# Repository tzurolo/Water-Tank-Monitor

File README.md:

# Water Tank Monitor
Monitors the water level in a tank that supplies the daily water to the Lion of Judah Academy campus of over 800 students.

You can see it in action with this ThingSpeak plugin: https://thingspeak.com/plugins/17358

Battery-powered IoT endpoint that posts data to a server via a cellular module.
Design goals:
1. run on batteries for **5 years**
2. post data to a server on the half hour
3. REPL over TCP/IP

## System details
Water level is measured using an ultrasonic distance sensor in the roof of the tank. It measures the
distance from the top of the tank to the surface of the water.

The key to running on batteries for a long time is the ability for the system to go into deep sleep.
The water level doesn't change quickly, so the system can sleep for several minutes between readings.
Power to the ultrasonic sensor and cellular module is switched on and off by a FET under microcontroller control. These devices get no power when the unit is sleeping.

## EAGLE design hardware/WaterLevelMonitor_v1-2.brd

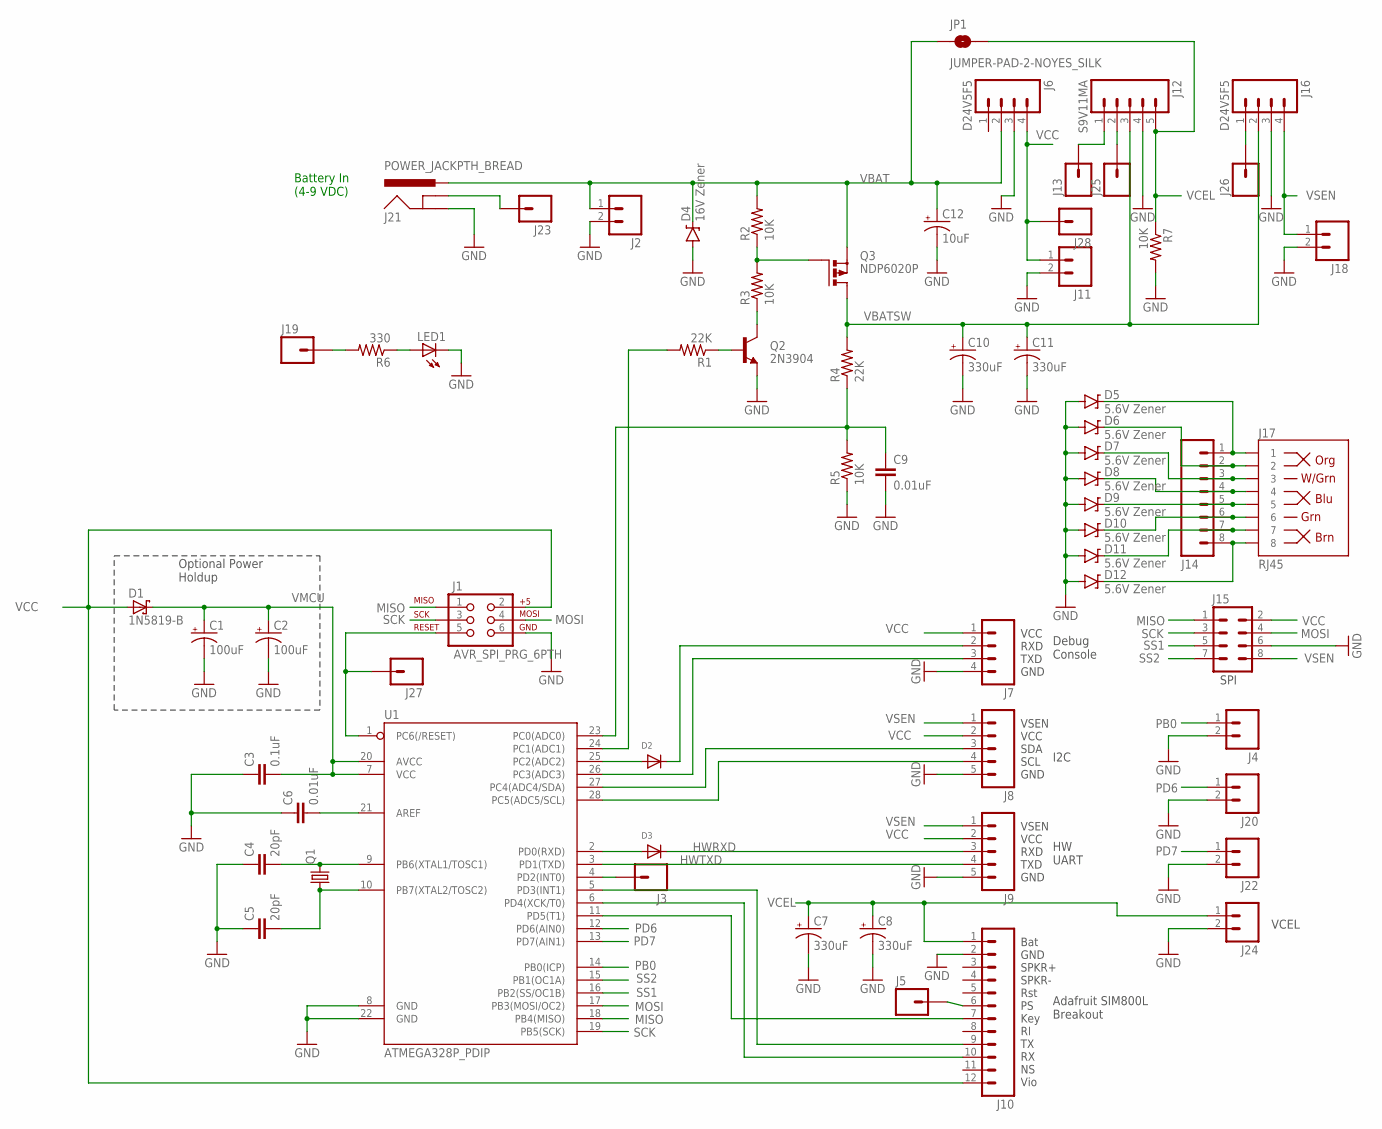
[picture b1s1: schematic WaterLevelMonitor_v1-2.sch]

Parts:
C1, C2: 100uF; CPOL-RADIAL-100UF-25V
C3: 0.1uF; CAP-PTH-SMALL
C4, C5: 20pF; CAP-PTH-SMALL
C6, C9: 0.01uF; CAP-PTH-5MM
C7, C8, C10, C11: 330uF; CPOL-RADIAL-100UF-25V
C12: 10uF; CPOL-RADIAL-100UF-25V
D1: 1N5819-B; DO41-7.6
D2, D3: DIODEDO-1N4148; DO-1N4148
D4: 16V Zener; DIODE-ZENER
D5, D6, D7, D8, D9, D10, D11, D12: 5.6V Zener; DIODE-ZENER
J1: AVR_SPI_PRG_6PTH; 2X3
J2, J11, J18, J24: M02PTH; 1X02
J3, J5, J13, J19, J23, J25, J26, J27, J28: M01PTH_NO_SILK_YES_STOP; 1X01_NO_SILK
J4, J20, J22: M021X02_NO_SILK; 1X02_NO_SILK
J6, J16: D24V5F5; 1X04
J7: M04PTH; 1X04
J8, J9: M05PTH; 1X05
J10: M12PTH; 1X12
J12: S9V11MA; 1X05
J14: M08SILK_FEMALE_PTH; 1X08
J15: M04X2; 2X4
J17: RJ45; RJ45-8
J21: POWER_JACKPTH_BREAD; POWER_JACK_PTH_BREAD
JP1: JUMPER-PAD-2-NOYES_SILK; PAD-JUMPER-2-NO_YES_SILK
LED1: LED5MM
Q1: CRYSTALHC49U-V; HC49U-V
Q2: 2N3904; TO-92-AMMO
Q3: NDP6020P; TO220BV
R1, R4: 22K; 0204/5
R2, R3, R5, R7: 10K; 0204/5
R6: 330; 0204/5
U1: ATMEGA328P_PDIP; DIL28-3

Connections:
GND: C1.2 (-), C2.2 (-), C3.1, C4.1, C5.1, C6.1, C7.2 (-), C8.2 (-), C9.2, C10.2 (-), C11.2 (-), C12.2 (-), D4.P$2 (A), D5.P$2 (A), D6.P$2 (A), D7.P$2 (A), D8.P$2 (A), D9.P$2 (A), D10.P$2 (A), D11.P$2 (A), D12.P$2 (A), J1.6, J2.2, J4.2, J6.3, J7.4, J8.5, J9.5, J10.2, J11.2, J12.4, J15.6, J16.3, J18.2, J20.2, J21.GND, J22.2, J24.2, LED1.K (C), Q2.1 (E), R5.1, R7.2, U1.8 (GND), U1.22 (GND)
HWRXD: D3.C, J9.3
HWTXD: J9.4, U1.3 (PD1(TXD))
MISO: J1.1, J15.1, U1.18 (PB4(MISO))
MOSI: J1.4, J15.4, U1.17 (PB3(MOSI/OC2))
unnamed: J10.7, U1.11 (PD5(T1))
unnamed: Q3.G, R2.1, R3.2
unnamed: Q2.2 (B), R1.1
unnamed: J10.9, U1.5 (PD3(INT1))
unnamed: J3.1, U1.4 (PD2(INT0))
unnamed: C9.1, R4.1, R5.2, U1.23 (PC0(ADC0))
unnamed: J10.10, U1.6 (PD4(XCK/T0))
unnamed: J19.1, R6.2
unnamed: C4.2, Q1.2, U1.9 (PB6(XTAL1/TOSC1))
unnamed: C5.2, Q1.1, U1.10 (PB7(XTAL2/TOSC2))
unnamed: C6.2, U1.21 (AREF)
unnamed: LED1.A, R6.1
unnamed: J5.1, J10.6
unnamed: Q2.3 (C), R3.1
unnamed: D3.A, U1.2 (PD0(RXD))
unnamed: J21.GNDBREAK, J23.1
unnamed: J12.2, J25.1
unnamed: J16.1, J26.1
unnamed: R1.2, U1.24 (PC1(ADC1))
unnamed: D2.A, U1.25 (PC2(ADC2))
unnamed: D2.C, J7.2
unnamed: J7.3, U1.26 (PC3(ADC3))
unnamed: D5.P$1 (C), J14.1, J17.1
unnamed: J12.1, J13.1
unnamed: J8.3, U1.27 (PC4(ADC4/SDA))
unnamed: J8.4, U1.28 (PC5(ADC5/SCL))
unnamed: D6.P$1 (C), J14.2, J17.2
unnamed: D7.P$1 (C), J14.3, J17.3
unnamed: D8.P$1 (C), J14.4, J17.4
unnamed: D9.P$1 (C), J14.5, J17.5
unnamed: J1.5, J27.1, U1.1 (PC6(/RESET))
unnamed: D10.P$1 (C), J14.6, J17.6
unnamed: D11.P$1 (C), J14.7, J17.7
unnamed: D12.P$1 (C), J14.8, J17.8
PB0: J4.1, U1.14 (PB0(ICP))
PD6: J20.1, U1.12 (PD6(AIN0))
PD7: J22.1, U1.13 (PD7(AIN1))
SCK: J1.3, J15.3, U1.19 (PB5(SCK))
SS1: J15.5, U1.16 (PB2(SS/OC1B))
SS2: J15.7, U1.15 (PB1(OC1A))
VBAT: C12.1 (+), D4.P$1 (C), J2.1, J6.2, J21.PWR, JP1.1, Q3.S, R2.2
VBATSW: C10.1 (+), C11.1 (+), J12.3, J16.2, Q3.D, R4.2
VCC: D1.A, J1.2, J6.4, J7.1, J8.2, J9.2, J10.12, J11.1, J15.2, J28.1
VCEL: C7.1 (+), C8.1 (+), J10.1, J12.5, J24.1, JP1.2, R7.1
VMCU: C1.1 (+), C2.1 (+), C3.2, D1.C, U1.7 (VCC), U1.20 (AVCC)
VSEN: J8.1, J9.1, J15.8, J16.4, J18.1

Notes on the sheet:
Battery In (4-9 VDC)
Optional Power Holdup
Adafruit SIM800L Breakout
Bat GND SPKR+ SPKR- Rst PS Key RI TX RX NS Vio
VSEN VCC SDA SCL GND
I2C
VSEN VCC RXD TXD GND
HW UART
Debug Console
VCC RXD TXD GND
SPI
VCEL

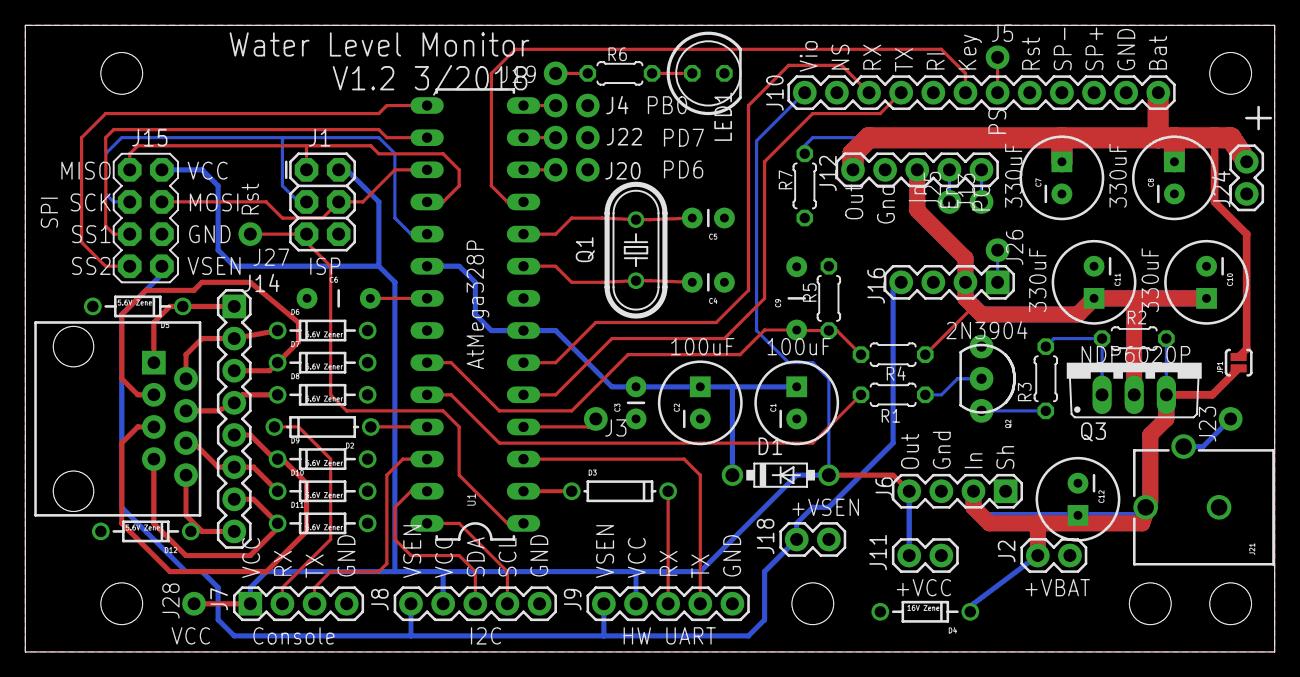
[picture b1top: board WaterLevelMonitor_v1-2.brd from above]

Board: 2 copper layers, 98.7 x 49.5 mm, 71 parts (0 on the bottom side), 51 nets.

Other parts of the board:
U$1, U$2, U$3, U$4, U$5, U$6: STAND-OFF

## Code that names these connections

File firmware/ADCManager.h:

//
//  Analog to Digital Converter Manager
//
//  Used to reserve the ADC and do conversions
//
//  Platform: AtMega328P
//
#ifndef ADCMANAGER_H
#define ADCMANAGER_H

#include <stdint.h>
#include <stdbool.h>
#include <avr/io.h>

// ADC voltage reference selection (use one only)
#define ADC_VOLTAGE_REF_AREF            0
#define ADC_VOLTAGE_REF_AVCC            1
#define ADC_VOLTAGE_REF_INTERNAL_1V1    3

// ADC single-ended input channels (use one only)
#define ADC_SINGLE_ENDED_INPUT_ADC0 0   // PC0
#define ADC_SINGLE_ENDED_INPUT_ADC1 1   // PC1
#define ADC_SINGLE_ENDED_INPUT_ADC2 2   // PC2
#define ADC_SINGLE_ENDED_INPUT_ADC3 3   // PC3
#define ADC_SINGLE_ENDED_INPUT_ADC4 4   // PC4
#define ADC_SINGLE_ENDED_INPUT_ADC5 5   // PC5
#define ADC_SINGLE_ENDED_INPUT_TEMP 8   // Temperature sensor
#define ADC_SINGLE_ENDED_INPUT_1V1  14  // I Ref
#define ADC_SINGLE_ENDED_INPUT_0V   15  // AGND

// called once at power-up
extern void ADCManager_Initialize (void);

// call once at the beginning of program after power-up for
// each channel you intend to use
extern void ADCManager_setupChannel (
    const uint8_t channel,  // one of ADC_SINGLE_ENDED_INPUT_xxx
    const uint8_t adcRef,   // one of ADC_VOLTAGE_REF_xxx
    const bool leftAdjustResult);

// schedules and reads the requested channel
// called in each iteration of the mainloop
extern void ADCManager_task (void);

// returns true and starts a conversion if the ADC is
// available (not in use by another caller).
// channel must be one of ADC_CHANNELn as defined in
// LUFA/Drivers/Peripheral/ADC.h
extern bool ADCManager_StartConversion (
    const uint8_t channelIndex);

// returns true when the conversion is complete and
// returns the analog value. only passes the value
// to the caller the first time it returns true
extern bool ADCManager_ConversionIsComplete (
    uint16_t* analogValue);

#endif  // ADCMANAGER_H

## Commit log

2017-04-12 more detail
2017-04-12 Create x
2017-04-20 software serial changes
    added 2nd software serial rx
    software serial tx now has 2 channels
2017-04-20 software serial
    added run-time bitfield I/O
2017-05-01 implemented ipconsole loop
2017-05-01 added -lm switch to recover 256 bytes RAM
2017-05-02 sleep with wdt wakeup with extended time
2017-05-11 formulas for sample and logging intervals
2017-06-02 Create f
2017-06-27 added DC power jack
2018-03-27 change console port, begin char range impl
2018-03-28 fixed Serial RX0 pin change interrupt vector
2018-04-21 implemented TCP/IP command loop
2018-04-22 partial update for CharStringSpan
2018-04-23 completed change to use CharStringSpan
2018-04-25 completed REPL over TCP/IP
2018-04-26 water level monitor task timeout
2018-04-27 fixed bug of clearing incoming command
2018-04-28 reboot logic
2018-04-28 settings, etc.
    watchdog timer calibration
    periodic reboot
    command prefix for SMS messages
    setters/getters
2018-04-30 reboot logic, more commands
2018-05-04 changed data packet format for easier parsing
2018-05-07 tweaks to self-reboot logic, CIPQSEND=0
2018-05-09 cipqsend option, level notification logic
2018-05-10 fixed bug in block command mode
2018-05-10 removed debug stmts
2018-05-19 reduced program size
2018-05-19 fixed bug in software serial upon wakeup
2018-05-21 Create placeholder
2018-05-22 system time accuracy, bug in powerdown state
2018-06-09 extend command, report water rising
2018-06-09 set notify rising, get notify
2018-06-23 CSTT username, password, rising level fix
2018-06-29 Default to Tanzania timezone
2018-07-04 increased server address size to 60
2018-07-04 increased server name size to 60
2018-07-06 pump data send to ThingSpeak
2018-07-14 added synthetic field for water level
2018-07-17 filter out invalid sensor readings
2018-08-02 get initial data from ThingSpeak, use ID field
2018-08-03 added PM2 installation
2018-08-03 add link to ThingSpeak plugin
2018-09-17 added simple "Kalman" filtering of sensor data
2018-10-11 reset tank empty distance parameter
    got value when tank went empty on 10/9/2018
2018-11-14 added bounds exception for dirty sensor

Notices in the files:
parts and their libraries:
SparkFun-Passives: Licensing: Creative Commons ShareAlike 4.0 International - https://creativecommons.org/licenses/by-sa/4.0
